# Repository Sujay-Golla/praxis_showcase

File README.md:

# Praxis II Showcase
## A Haptics-based Remote-Controlled Automated GoPro Lever
By: Julia Gadsdon, Sujay Golla, Alina Zheng, Echo Zhu

https://github.com/user-attachments/assets/2c1850a1-496b-431b-8701-bd82d0e33e97

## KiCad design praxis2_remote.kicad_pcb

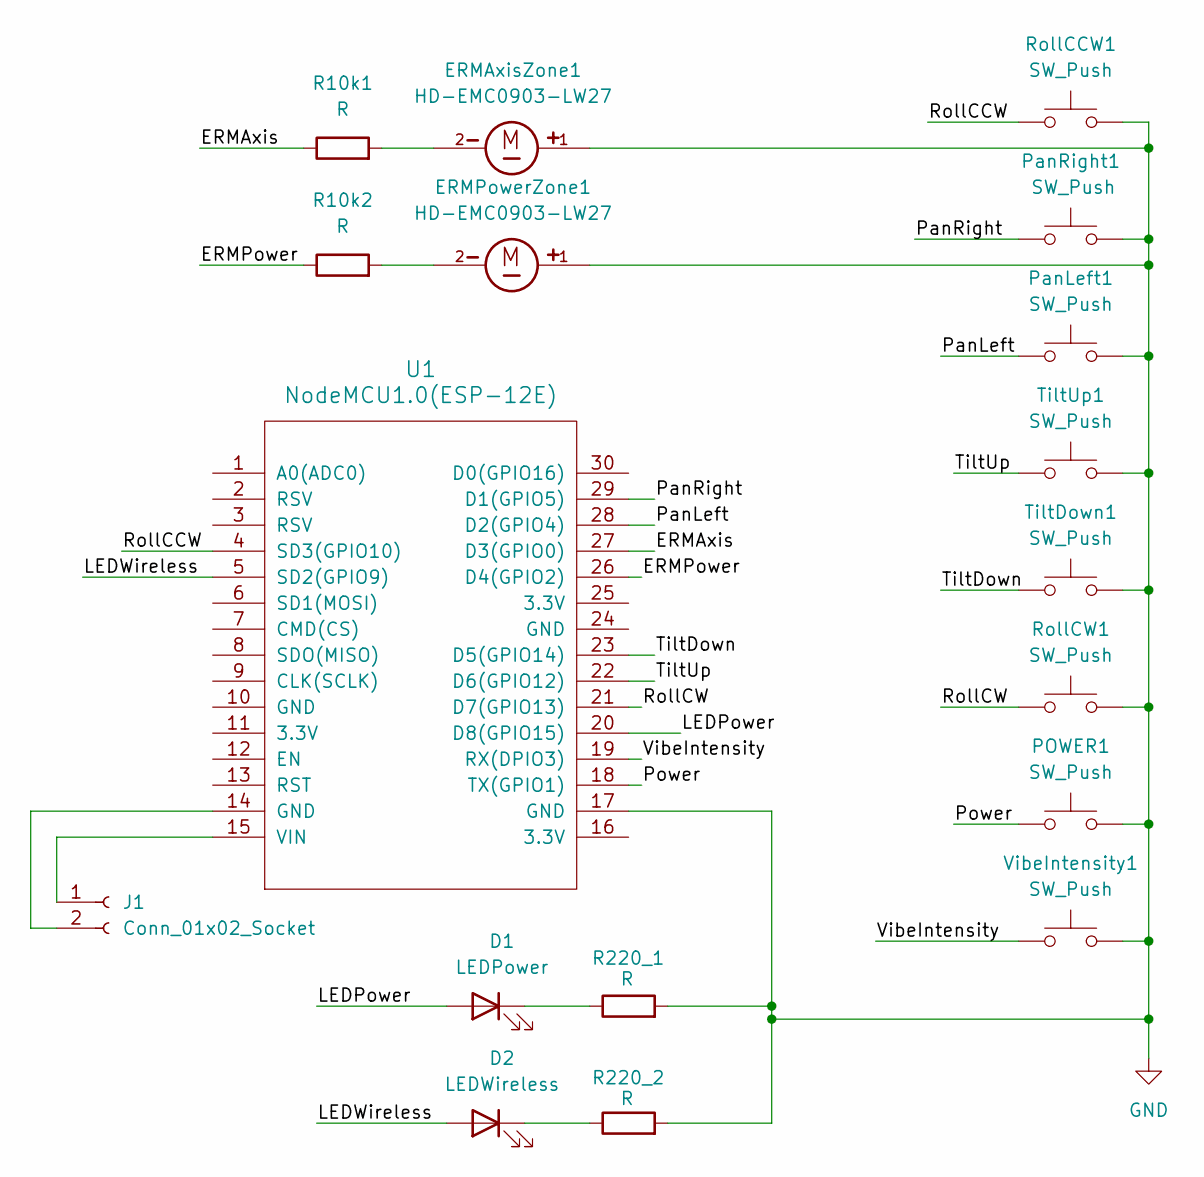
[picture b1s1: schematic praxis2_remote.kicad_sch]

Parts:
D1: LEDPower; LED_D5.0mm
D2: LEDWireless; LED_D5.0mm
ERMAxisZone1: HD-EMC0903-LW27; PinHeader_1x02_P2.54mm_Vertical; PARTREV A
ERMPowerZone1: HD-EMC0903-LW27; PinHeader_1x02_P2.54mm_Vertical; PARTREV A
J1: Conn_01x02_Socket; PinHeader_1x02_P2.54mm_Vertical
POWER1: SW_Push; SW_PUSH_6mm
PanLeft1: SW_Push; SW_PUSH_6mm
PanRight1: SW_Push; SW_PUSH_6mm
R10k1, R10k2, R220_1, R220_2: R; R_Axial_DIN0207_L6.3mm_D2.5mm_P7.62mm_Horizontal
RollCCW1: SW_Push; SW_PUSH_6mm
RollCW1: SW_Push; SW_PUSH_6mm
TiltDown1: SW_Push; SW_PUSH_6mm
TiltUp1: SW_Push; SW_PUSH_6mm
U1: NodeMCU1.0(ESP-12E); NodeMCU1.0(12-E)
VibeIntensity1: SW_Push; SW_PUSH_6mm

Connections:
/ERMAxis: R10k1.1, U1.27 (D3(GPIO0))
/ERMPower: R10k2.1, U1.26 (D4(GPIO2))
/LEDPower: D1.2 (A), U1.20 (D8(GPIO15))
/LEDWireless: D2.2 (A), U1.5 (SD2(GPIO9))
/PanLeft: PanLeft1.1, U1.28 (D2(GPIO4))
/PanRight: PanRight1.1, U1.29 (D1(GPIO5))
/Power: POWER1.1, U1.18 (TX(GPIO1))
/RollCCW: RollCCW1.1, U1.4 (SD3(GPIO10))
/RollCW: RollCW1.1, U1.21 (D7(GPIO13))
/TiltDown: TiltDown1.1, U1.23 (D5(GPIO14))
/TiltUp: TiltUp1.1, U1.22 (D6(GPIO12))
/VibeIntensity: U1.19 (RX(DPIO3)), VibeIntensity1.1
GND: ERMAxisZone1.1, ERMPowerZone1.1, POWER1.2, PanLeft1.2, PanRight1.2, R220_1.2, R220_2.2, RollCCW1.2, RollCW1.2, TiltDown1.2, TiltUp1.2, U1.17 (GND), VibeIntensity1.2
unnamed: D1.1 (K), R220_1.1
unnamed: D2.1 (K), R220_2.1
unnamed: ERMAxisZone1.2, R10k1.2
unnamed: ERMPowerZone1.2, R10k2.2
unnamed: J1.1, U1.15 (VIN)
unnamed: J1.2, U1.14 (GND)

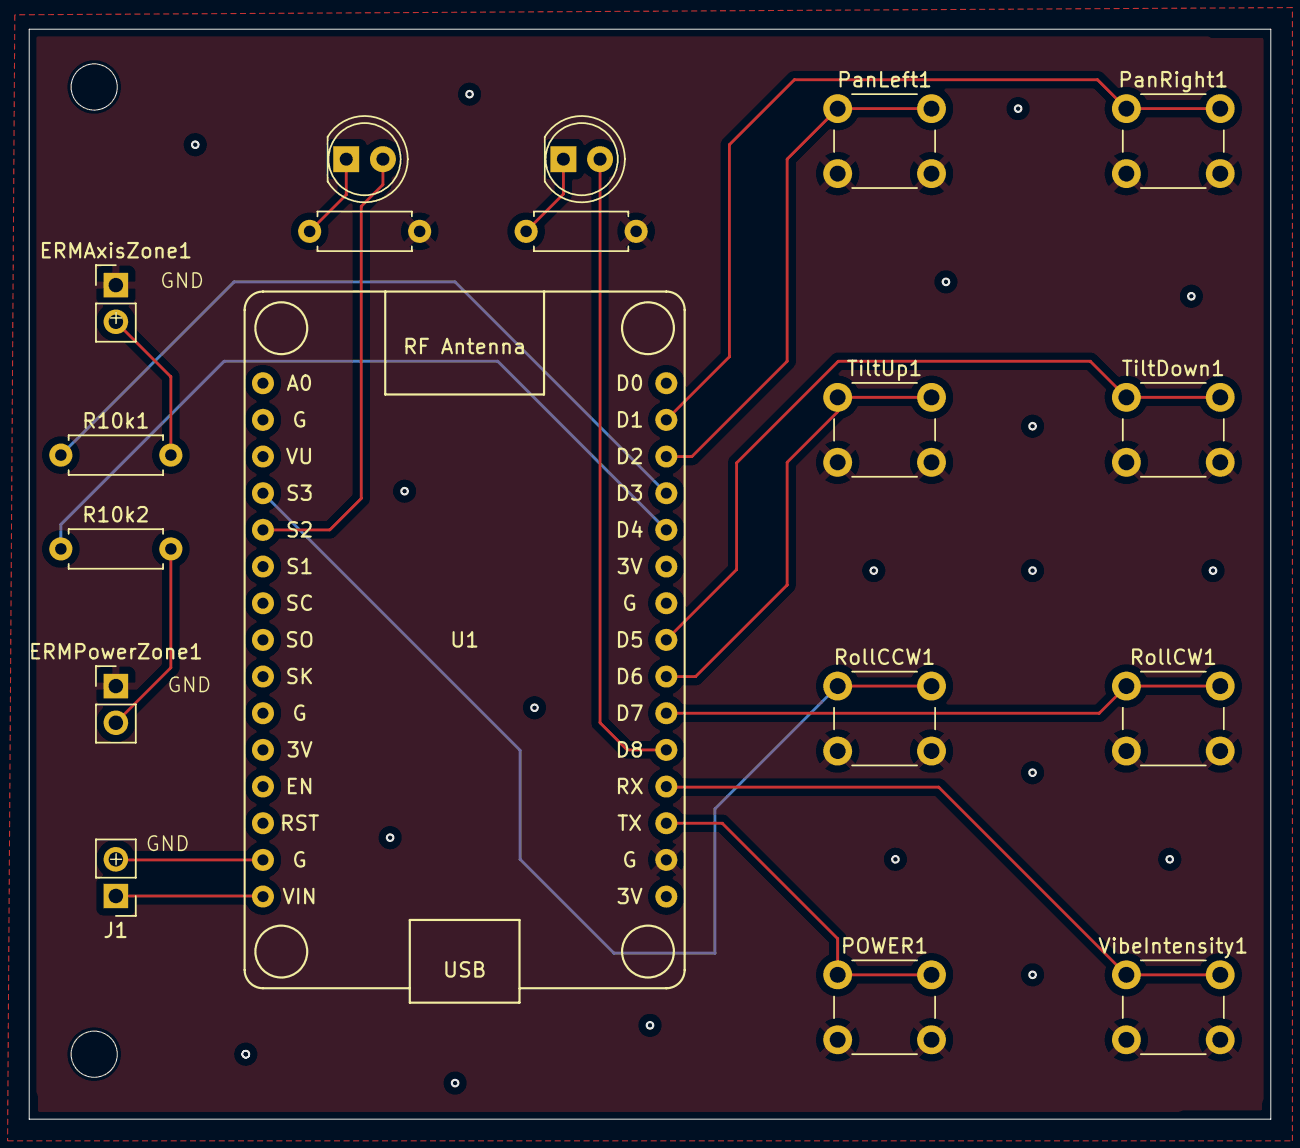
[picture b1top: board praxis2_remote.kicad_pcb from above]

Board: 2 copper layers, 86.0 x 75.5 mm, 18 parts (0 on the bottom side), 19 nets.

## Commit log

2026-03-25 final
2026-03-25 more final files
2026-05-18 Add project description to README.md
2026-05-18 Add project subtitle to README
